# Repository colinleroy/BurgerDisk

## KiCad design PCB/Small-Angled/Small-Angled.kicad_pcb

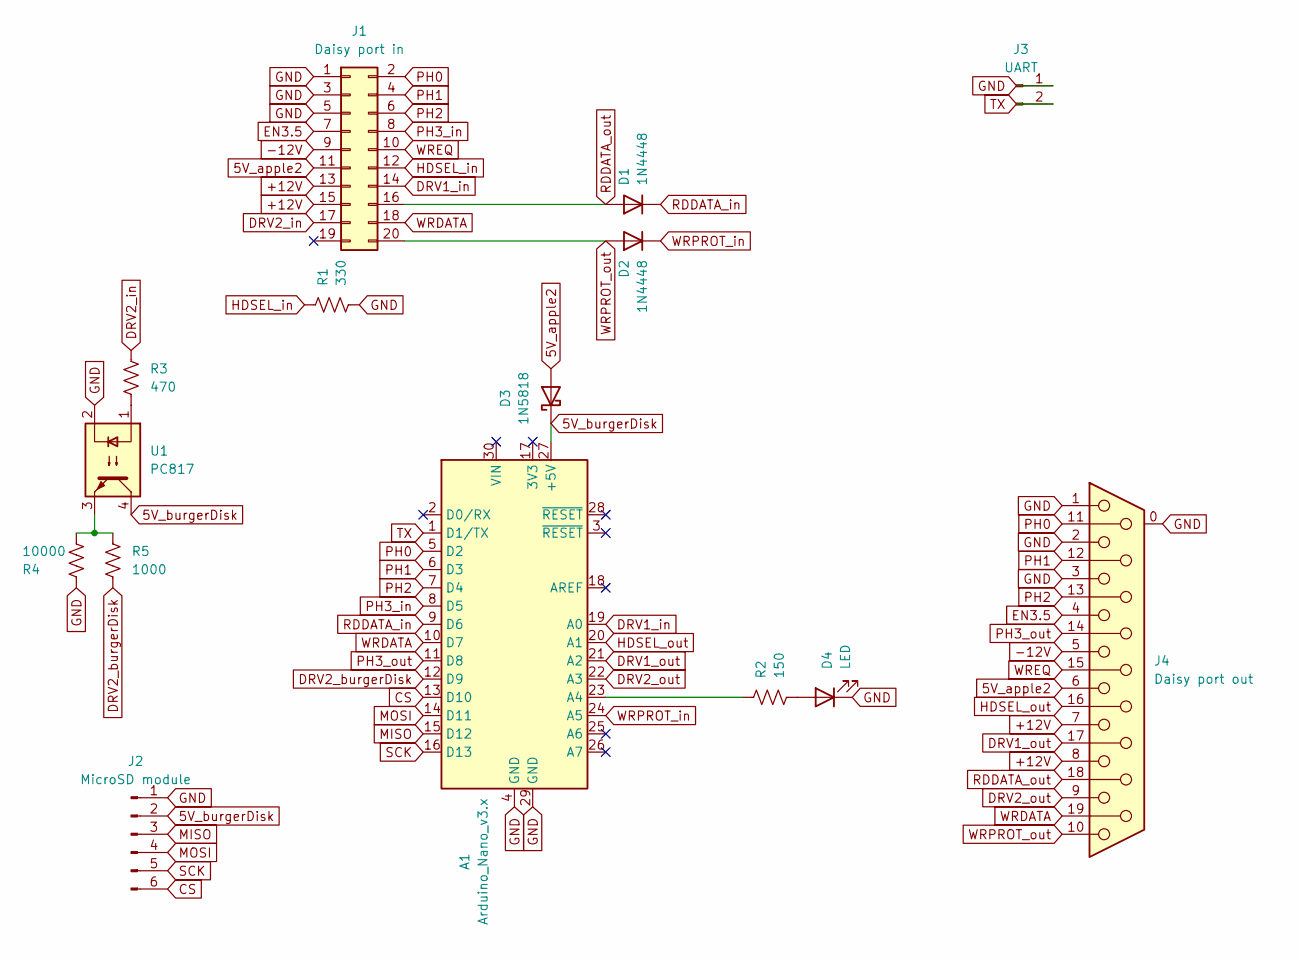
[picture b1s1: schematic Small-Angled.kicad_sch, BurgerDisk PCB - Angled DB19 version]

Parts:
A1: Arduino_Nano_v3.x; Arduino_Nano
D1, D2: 1N4448; D_DO-35_SOD27_P7.62mm_Horizontal; LCSC C258170
D3: 1N5818; D_DO-41_SOD81_P7.62mm_Horizontal; LCSC C402217
D4: LED; PinHeader_1x02_P2.54mm_Vertical; LCSC C6273326
J1: Daisy port in; IDC-Header_2x10_P2.54mm_Vertical; LCSC C305958
J2: MicroSD module; PinHeader_1x06_P2.54mm_Vertical; LCSC C6209271
J3: UART; PinHeader_1x02_P2.54mm_Vertical; LCSC C6273326
J4: Daisy port out; DSUB-19_Female_Horizontal_P2.77x2.84mm_EdgePinOffset4.94mm_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
R1: 330; R_Axial_DIN0207_L6.3mm_D2.5mm_P7.62mm_Horizontal; LCSC C58608
R2: 150; R_Axial_DIN0207_L6.3mm_D2.5mm_P7.62mm_Horizontal; LCSC C58668
R3: 470; R_Axial_DIN0309_L9.0mm_D3.2mm_P12.70mm_Horizontal; LCSC C129899
R4: 10000; R_Axial_DIN0207_L6.3mm_D2.5mm_P7.62mm_Horizontal; LCSC C57436
R5: 1000; R_Axial_DIN0207_L6.3mm_D2.5mm_P7.62mm_Horizontal; LCSC C57435
U1: PC817; DIP-4_W7.62mm; LCSC C5350

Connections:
5V_apple2: D3.2 (A), J1.11, J4.6
5V_burgerDisk: A1.27 (+5V), D3.1 (K), J2.2, U1.4
+12V: J1.13, J1.15, J4.7, J4.8
-12V: J1.9, J4.5
CS: A1.13 (D10), J2.6
DRV1_in: A1.19 (A0), J1.14
DRV1_out: A1.21 (A2), J4.17
DRV2_burgerDisk: A1.12 (D9), R5.1
DRV2_in: J1.17, R3.1
DRV2_out: A1.22 (A3), J4.9
EN3.5: J1.7, J4.4
GND: A1.4 (GND), A1.29 (GND), D4.1 (K), J1.1, J1.3, J1.5, J2.1, J3.1, J4.0, J4.1, J4.2, J4.3, R1.1, R4.1, U1.2
HDSEL_in: J1.12, R1.2
HDSEL_out: A1.20 (A1), J4.16
MISO: A1.15 (D12), J2.3
MOSI: A1.14 (D11), J2.4
unnamed: A1.23 (A4), R2.2
unnamed: D4.2 (A), R2.1
unnamed: R3.2, U1.1
unnamed: R4.2, R5.2, U1.3
PH0: A1.5 (D2), J1.2, J4.11
PH1: A1.6 (D3), J1.4, J4.12
PH2: A1.7 (D4), J1.6, J4.13
PH3_in: A1.8 (D5), J1.8
PH3_out: A1.11 (D8), J4.14
RDDATA_in: A1.9 (D6), D1.1 (K)
RDDATA_out: D1.2 (A), J1.16, J4.18
SCK: A1.16 (D13), J2.5
TX: A1.1 (D1/TX), J3.2
WRDATA: A1.10 (D7), J1.18, J4.19
WREQ: J1.10, J4.15
WRPROT_in: A1.24 (A5), D2.1 (K)
WRPROT_out: D2.2 (A), J1.20, J4.10

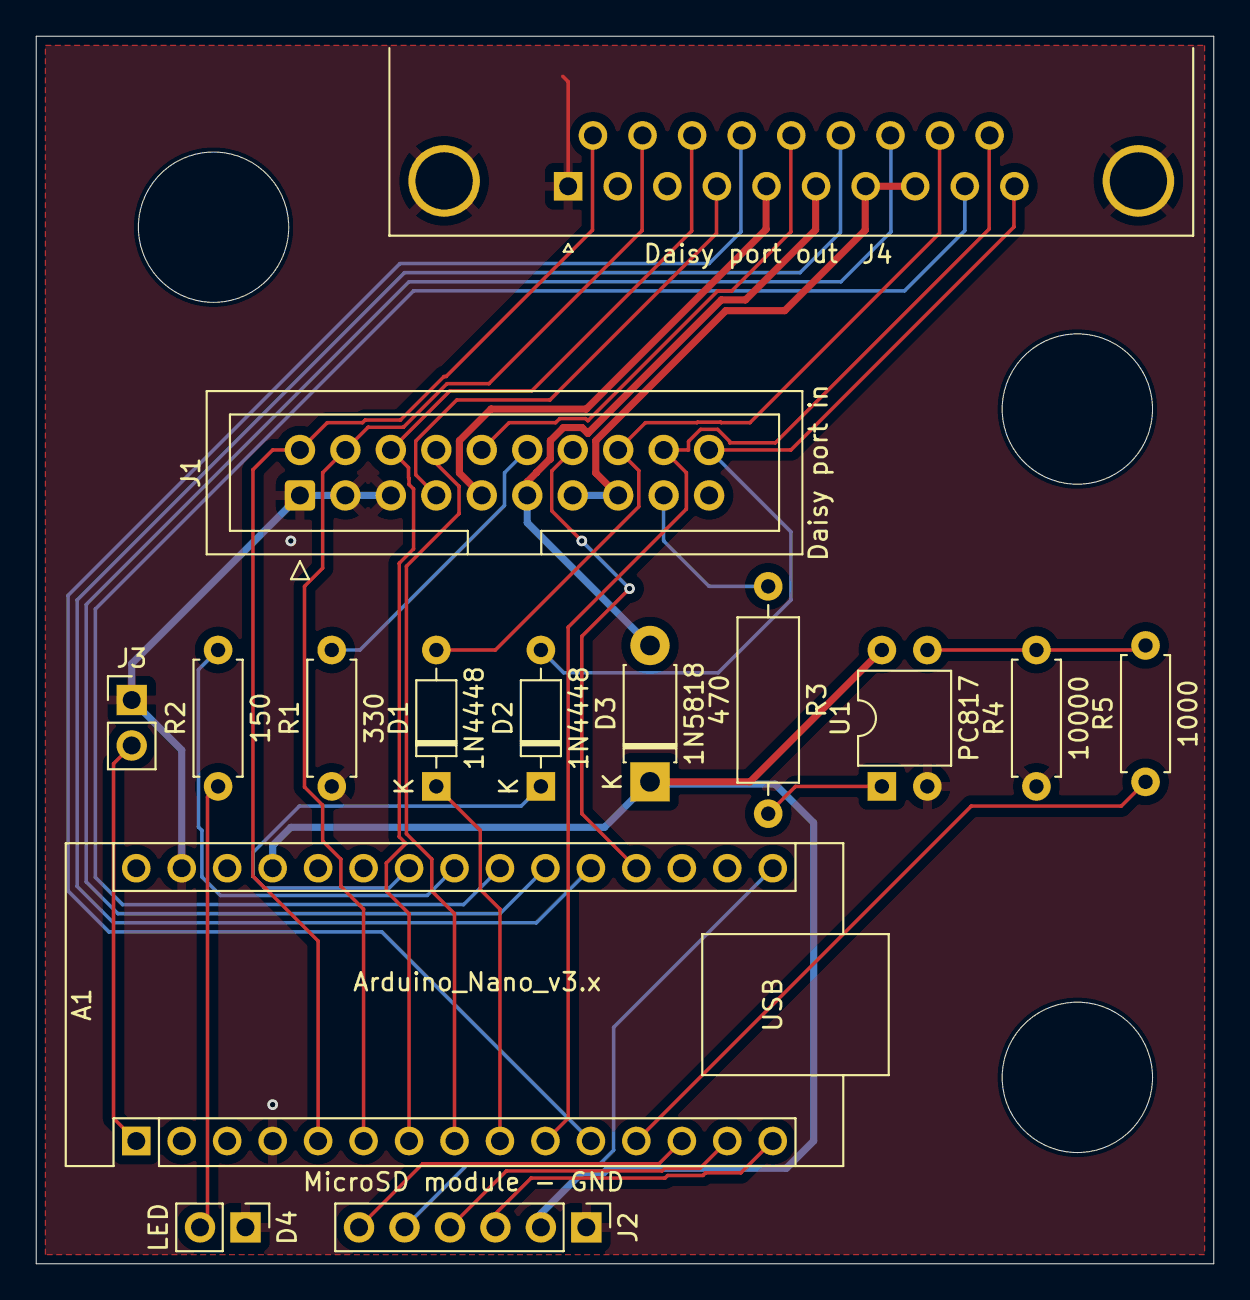
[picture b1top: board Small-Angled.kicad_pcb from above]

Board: 2 copper layers, 65.8 x 68.6 mm, 15 parts (0 on the bottom side), 33 nets.

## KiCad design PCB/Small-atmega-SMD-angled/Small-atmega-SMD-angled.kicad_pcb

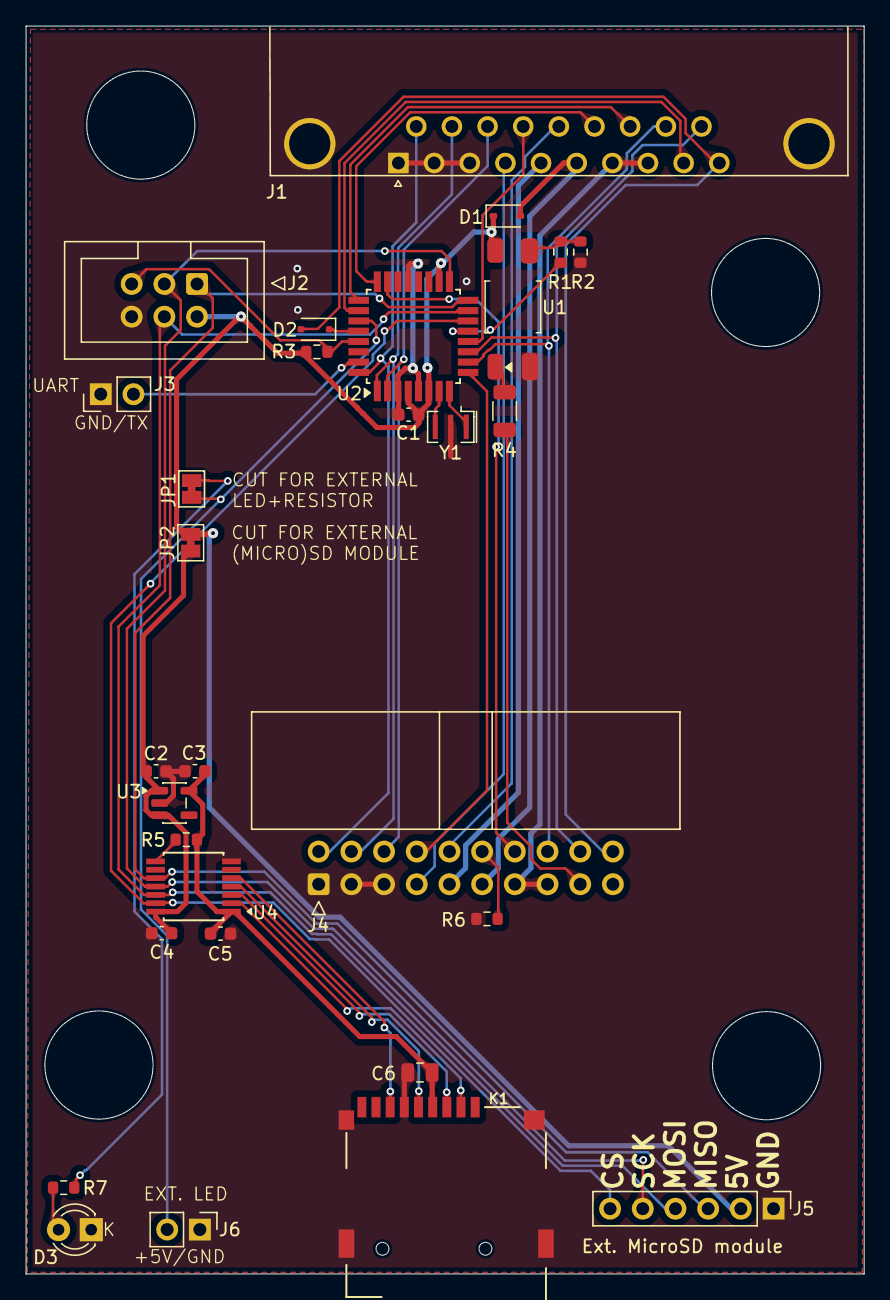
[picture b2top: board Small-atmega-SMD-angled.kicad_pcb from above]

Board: 2 copper layers, 65.1 x 96.9 mm, 30 parts (0 on the bottom side), 43 nets.

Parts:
C1, C4, C5: 100n; C_0603_1608Metric
C2, C3: 2u2; C_0603_1608Metric
C6: 22uf; C_0805_2012Metric
D1: 1N5818WS; D_SOD-323
D2: 1N4448WS; D_SOD-323F
D3: LED; LED_D3.0mm
J1: Daisy port out; DSUB-19_Female_Horizontal_MXS82009-8251-9246
J2: ICSP_ISP6; IDC-Header_2x03_P2.54mm_Vertical
J3, J6: 2-pin header; PinHeader_1x02_P2.54mm_Vertical
J4: Daisy port in; IDC-Header_2x10_P2.54mm_Horizontal
J5: Ext. MicroSD module; PinHeader_1x06_P2.54mm_Vertical
JP1: INT/EXT LED JUMPER; SolderJumper-2_P1.3mm_Bridged_Pad1.0x1.5mm
JP2: INT MICROSD JUMPER; SolderJumper-2_P1.3mm_Bridged_Pad1.0x1.5mm
K1: HYC77-TF09-200; MICROSD-HYC77-TF09-200
R1: 1k; R_0603_1608Metric
R2, R5: 10k; R_0603_1608Metric
R3: 10K; R_0603_1608Metric
R4: 470; R_1206_3216Metric
R6: 330; R_0603_1608Metric
R7: 150; R_0603_1608Metric
U1: PC817C-S; SOP-4_3.8x4.1mm_P2.54mm
U2: ATmega328P-AU; TQFP-32_7x7mm_P0.8mm
U3: SE5218; SOT-23-5
U4: TXB0104PWR; TSSOP-14-1EP_4.4x5mm_P0.65mm
Y1: Resonator_GND2; Resonator_SMD_Murata_CSTxExxV-3Pin_3.0x1.1mm

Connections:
3V3: C3.2, C5.1, C6.2, K1.4 (VDD), R5.1, U3.5 (VOUT), U4.1 (VCCA)
5V_apple2: D1.2 (A), J1.6, J4.11
5V_burgerDisk: C1.1, D1.1 (K), J2.2, J5.2, JP2.2 (B), R3.1, U1.4, U2.4 (VCC), U2.6 (VCC), U2.18 (AVCC)
5V_intMicroSD: C2.2, C4.2, JP2.1 (A), U3.1 (VIN), U3.3 (EN), U4.14 (VCCB)
+12V: J1.7, J1.8, J4.13, J4.15
-12V: J1.5, J4.9
CS: J5.6, U2.14 (PB2), U4.13 (B1)
CS_L: K1.2 (CS), U4.2 (A1)
DRV1_in: J4.14, U2.23 (PC0)
DRV1_out: J1.17, U2.25 (PC2)
DRV2_burgerDisk: R1.1, U2.13 (PB1)
DRV2_in: J4.17, R4.1
DRV2_out: J1.9, U2.26 (PC3)
EN3.5: J1.4, J4.7
GND: C1.2, C2.1, C3.1, C4.1, C5.2, C6.1, D3.1 (K), J1.0, J1.1, J1.2, J1.3, J2.6, J3.1, J4.1, J4.3, J4.5, J5.1, J6.1 (+5V), K1.6 (GND), K1.SHIELD, R2.1, R6.1, U1.2, U2.3 (GND), U2.5 (GND), U2.21 (GND), U3.2 (GND), U4.7 (GND), Y1.2
HDSEL_in: J4.12, R6.2
HDSEL_out: J1.16, U2.24 (PC1)
LED: J6.2 (GND), JP1.2 (B), U2.27 (PC4)
MISO: J2.1, J5.3, U2.16 (PB4), U4.10 (B4)
MISO_L: K1.7 (MISO), U4.5 (A4)
MOSI: J2.4, J5.4, U2.15 (PB3), U4.12 (B2)
MOSI_L: K1.3 (MOSI), U4.3 (A2)
unnamed: D3.2 (A), R7.1
unnamed: JP1.1 (A), R7.2
unnamed: R1.2, R2.2, U1.3
unnamed: R4.2, U1.1
unnamed: U2.7 (XTAL1/PB6), Y1.3
unnamed: U2.8 (XTAL2/PB7), Y1.1
OE: R5.2, U4.8 (OE)
PH0: J1.11, J4.2, U2.32 (PD2)
PH1: J1.12, J4.4, U2.1 (PD3)
PH2: J1.13, J4.6, U2.2 (PD4)
PH3_in: J4.8, U2.9 (PD5)
PH3_out: J1.14, U2.12 (PB0)
RDDATA: J1.18, J4.16, U2.10 (PD6)
RESET: J2.5, R3.2, U2.29 (~RESET/PC6)
SCK: J2.3, J5.5, U2.17 (PB5), U4.11 (B3)
SCLK_L: K1.5 (SCLK), U4.4 (A3)
TX: J3.2, U2.31 (PD1)
WRDATA: J1.19, J4.18, U2.11 (PD7)
WREQ: J1.15, J4.10
WRPROT_in: D2.1 (K), U2.28 (PC5)
WRPROT_out: D2.2 (A), J1.10, J4.20

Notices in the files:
PCB/Small-Angled/Small-Angled.kicad_pcb:
BurgerDisk - CC BY-SA
© Colin Leroy-Mira 2026
PCB/Small-Angled/Small-Angled.kicad_sch:
License: CC BY-SA
